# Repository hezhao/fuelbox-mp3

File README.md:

Fuelbox MP3
===========

* v1v2: An mp3 player controller board with LM386 op-amp, using touch sensor, push button and light sensor as trigger.
* v3: An mp3 player + Arduino + TPA2005D1 amp all-in-one triggered only by SPST-NC reed switch (SPDT will do too, just choose NC pair). Once triggered, Arduino checks the EEPROM flag, plays the audio once, and sleeps forever.

Power Consumption
=================
* Arduino Pro Mini 5V + MP3 module + TPA2005D1 amp = 50mA @ 7.4V
* Arduino Pro Mini 5V = 15mA @ 5V
* TPA2005D1 = 15mA @ 5V
* Sleep Mode: Arduino Pro Mini 5V = 0.58mA @ 9V
* Sleep Mode: TPA2005D1 = 0.5µA @ 5V (datasheet)
* Limits: 2032 Battery max discharge = 10mA @ 3V
* Limits: Arduino digital pin max output current = 40mA
* Limits: Arduino VCC-GNC max output current = 200mA

Notes
=====
* When using LiPo battery, there is a large inrust current. A 30Ω current limiting resistor is placed in serial with reed switch. However, limiting resistor is not necessary with for TPA2005D1
* <del> R = U / Switching Current = 7.4V / 0.25A = 29.6Ω; For absolute safety, use R = 8.2V / 0.25A = 32.8Ω since fully charged LiPo battery can reach 4.2V </del>
* TPA2005D1 amp produces a short bust sound if triggered by the arduino digital pin, so instead it is directly powered by VCC and digital pin 9 shutsdown amp after audio finishes

TODO
====
* v2: TOUCH sensor is not supposed to be grounded (GND plane may cause problem)
* v2: Remove vias that connect to TOUCH sensor

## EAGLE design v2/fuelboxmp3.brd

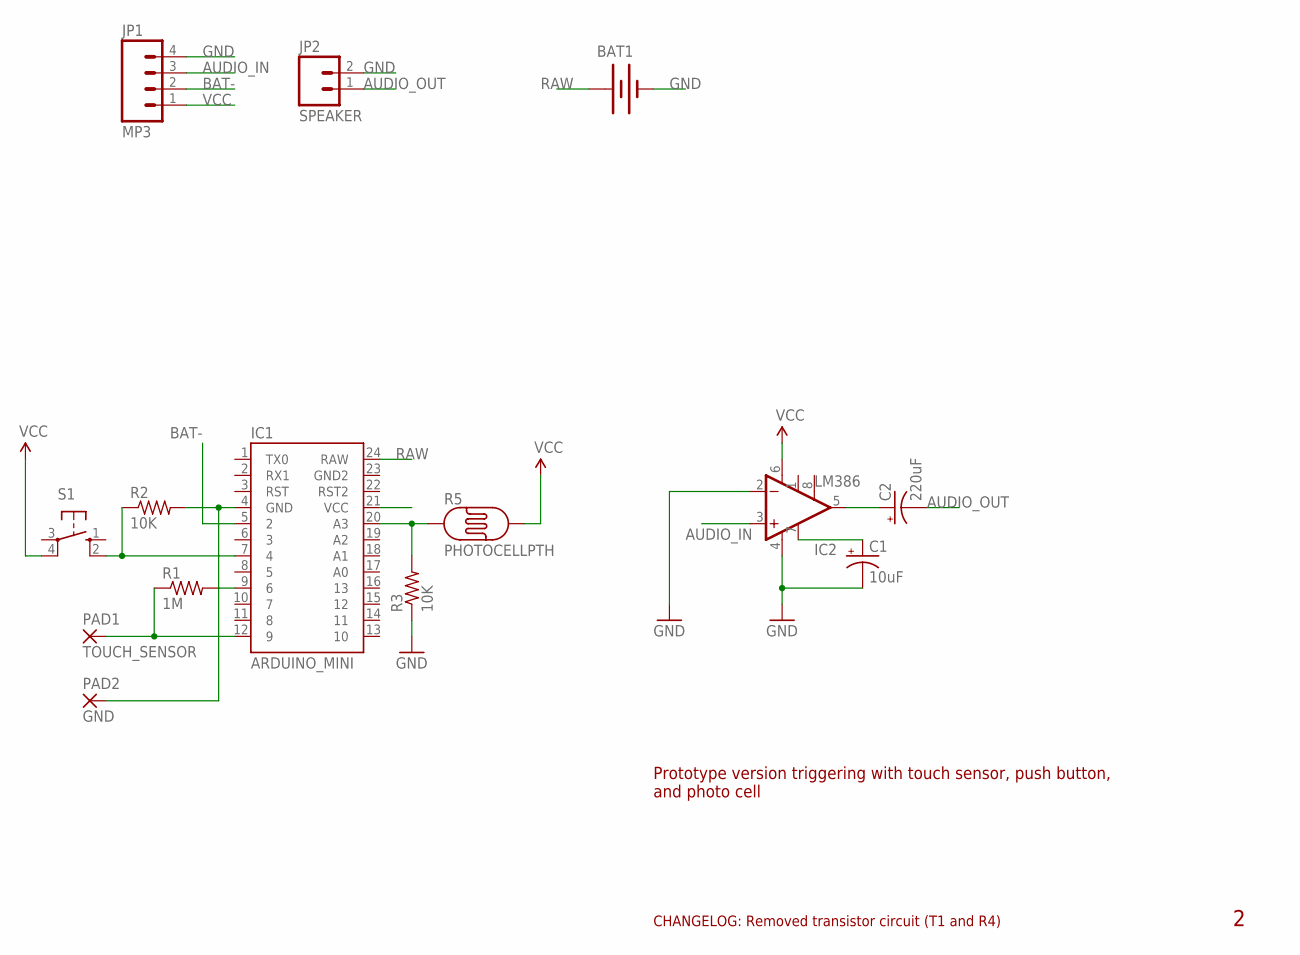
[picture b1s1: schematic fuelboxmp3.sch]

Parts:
BAT1: BATTERY1100; LIPO-1100MAH
C1: 10uF; E2,5-5
C2: 220uF; E2,5-6
IC1: ARDUINO_MINI
IC2: LM386; DIP08
JP1: MP3; 1X04
JP2: SPEAKER; 1X02
PAD1: TOUCH_SENSOR; 3,81/1,1
PAD2: GND; 3,81/1,1
R1: 1M; 0204/7
R2, R3: 10K; 0204/7
R5: PHOTOCELLPTH; PHOTOCELL
S1: 10-XX; B3F-10XX

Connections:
AUDIO_IN: IC2.3 (+IN), JP1.3
AUDIO_OUT: C2.-, JP2.1
BAT-: IC1.5 (2), JP1.2
GND: BAT1.-, C1.-, IC1.4 (GND), IC2.2 (-IN), IC2.4 (V-), JP1.4, JP2.2, PAD2.1, R2.2, R3.1
unnamed: IC1.9 (6), R1.2
unnamed: IC1.12 (9), PAD1.1, R1.1
unnamed: C2.+, IC2.5 (OUT)
unnamed: IC1.7 (4), R2.1, S1.2 (S1)
unnamed: IC1.20 (A3), R3.2, R5.1
unnamed: C1.+, IC2.7 (BP)
RAW: BAT1.+, IC1.24 (RAW)
VCC: IC1.21 (VCC), IC2.6 (V+), JP1.1, R5.2, S1.4 (P1)

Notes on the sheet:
Prototype version triggering with touch sensor, push button, and photo cell
CHANGELOG: Removed transistor circuit (T1 and R4)

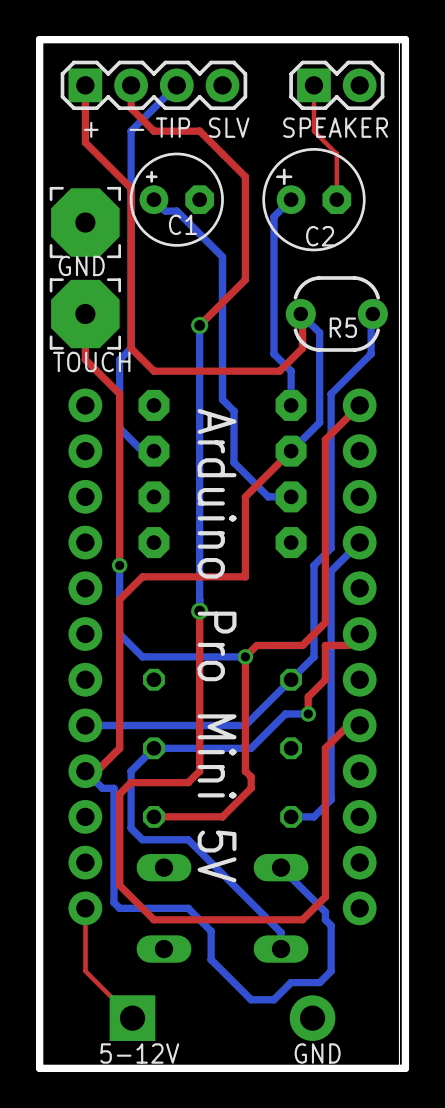
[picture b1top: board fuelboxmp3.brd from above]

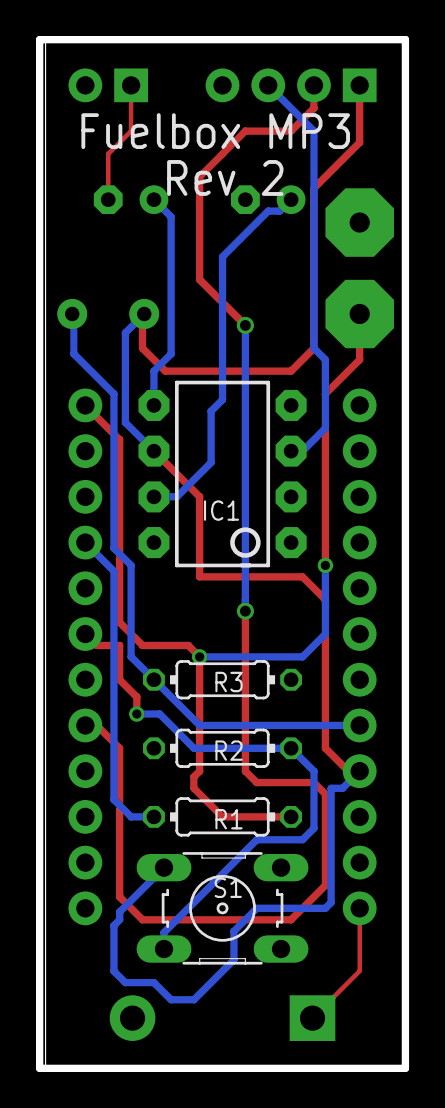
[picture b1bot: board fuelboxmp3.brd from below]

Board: 2 copper layers, 20.3 x 57.1 mm, 14 parts (5 on the bottom side), 12 nets.

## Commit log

2013-11-04 submitted to OSH Park
2013-12-03 add arduino code v2
2013-12-03 version 2: removed transistor circuit T1 and R4 because BAT- was GND when open. BAT- now connects directly to Pin 2
2014-01-23 version 3 no pcb
2014-01-27 use audioPin = 4, add circuit drawing
2014-01-27 change image size
2014-01-29 use sparkfun TPA2005D1 amp, use pin 9 as shutdown pin
2014-01-29 update README, explains amp bust sound issue and solution
2014-02-03 update circuit diagram
2014-02-06 add prototype picture
2014-02-06 fix image width in README
2014-02-06 fix image width again
2014-02-06 delte prototype.png
2014-02-06 add prototype.png back
2014-02-06 use raw instead of raw2 for image url
2014-02-26 added bom
2014-03-03 add more pics

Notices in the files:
parts and their libraries:
SparkFun-Boards: Licensing: CC v3.0 Share-Alike You are welcome to use this library for commercial purposes.
